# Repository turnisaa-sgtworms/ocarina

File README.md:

# ocarina
30key reversible monobody split, halves attached together by a n!n or promicro.

choc v1, mbk spaced.

firmware is available but the default keymap may be wonky

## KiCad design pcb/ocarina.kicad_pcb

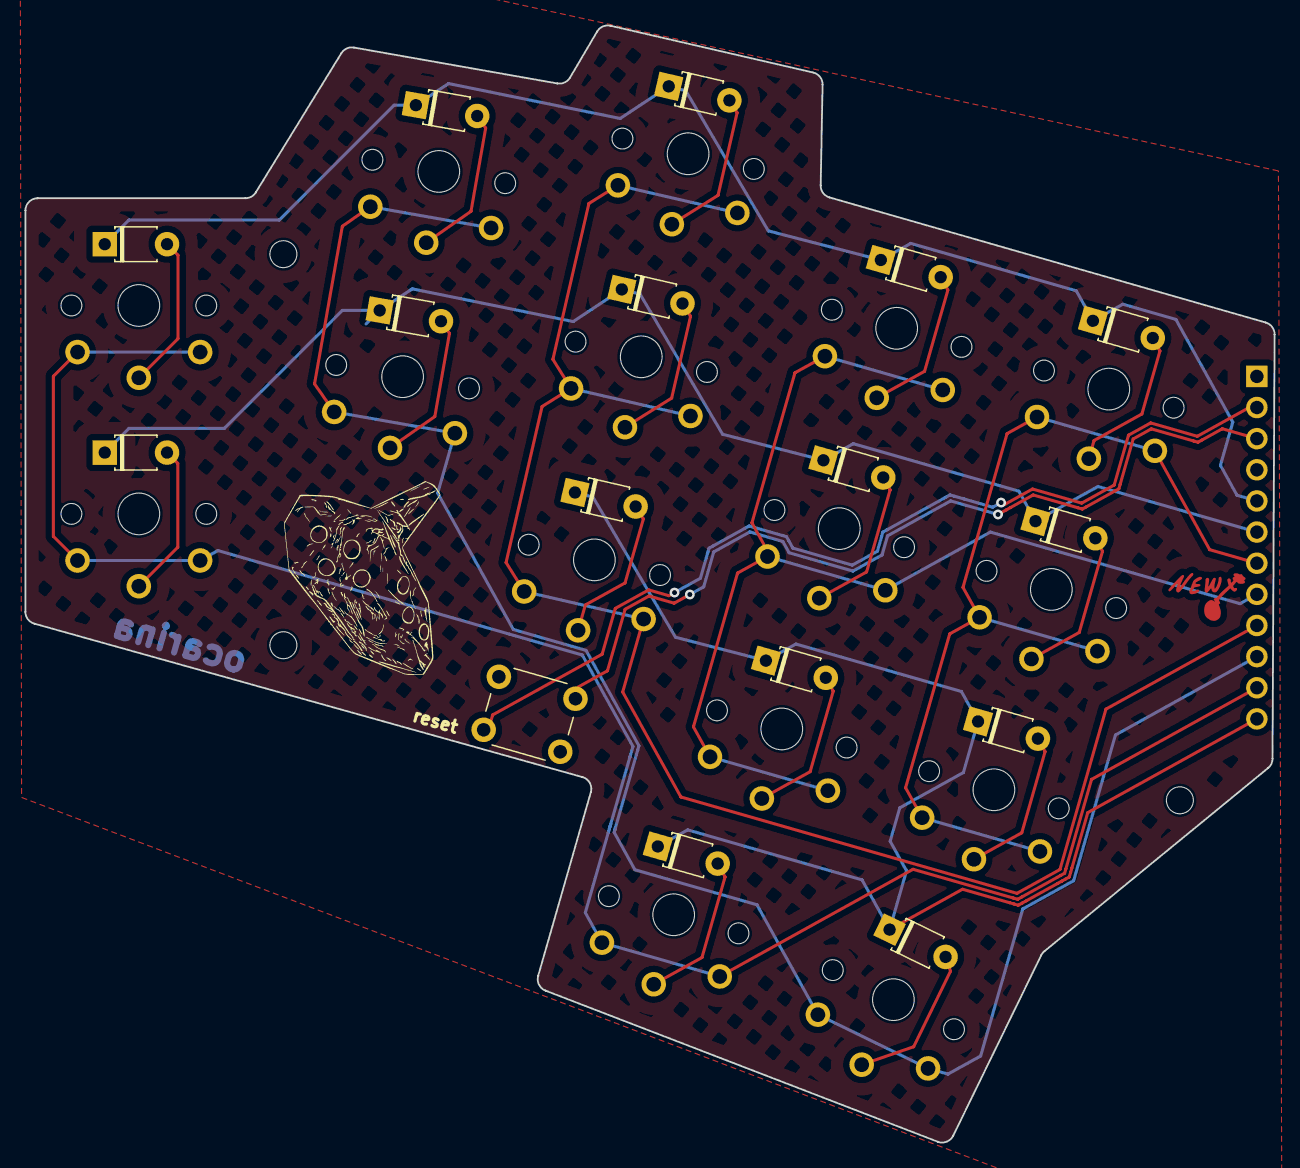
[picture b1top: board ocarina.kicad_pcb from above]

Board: 2 copper layers, 101.9 x 91.1 mm, 31 parts (0 on the bottom side), 23 nets.

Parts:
D1, D2, D3, D4, D5, D6, D7, D8, D9, D10, D11, D12, D13, D14, D15: 5mm diode
MCU1: ProMicro
S1, S2, S3, S4, S5, S6, S7, S8, S9, S10, S11, S12, S13, S14, S15: SW_choc_no_silk

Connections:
P10: D5.1, D8.1, D11.1, D14.1, D15.1, MCU1.12
P14: MCU1.10, S3.1, S4.1, S15.1
P15: MCU1.9, S5.1, S6.1, S7.1
P16: MCU1.11, S1.1, S2.1, S14.1
P18: MCU1.8, S8.1, S9.1, S10.1
P19: MCU1.7, S11.1, S12.1, S13.1
P20: D1.1, D3.1, D6.1, D9.1, D12.1, MCU1.6
P21: D2.1, D4.1, D7.1, D10.1, D13.1, MCU1.5
home_thumb: D15.2, S15.2
index_bottom: D8.2, S8.2
index_home: D9.2, S9.2
index_top: D10.2, S10.2
inner_bottom: D11.2, S11.2
inner_home: D12.2, S12.2
inner_top: D13.2, S13.2
middle_bottom: D5.2, S5.2
middle_home: D6.2, S6.2
middle_top: D7.2, S7.2
near_thumb: D14.2, S14.2
pinky_home: D1.2, S1.2
pinky_top: D2.2, S2.2
ring_home: D3.2, S3.2
ring_top: D4.2, S4.2

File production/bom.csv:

Designator,Footprint,Quantity,Value,LCSC Part #
"D1, D10, D11, D12, D13, D14, D15, D2, D3, D4, D5, D6, D7, D8, D9",5mm diode,15,,
MCU1,ProMicro,1,,

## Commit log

2025-06-28 initial commit (pcb, gerber)
2025-06-28 added images
2025-06-28 added ergogen file
2025-06-28 added case files
2025-06-29 added firmware
